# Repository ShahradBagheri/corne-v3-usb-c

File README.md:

# Corne Cherry v3 with a USB-C split link

Open `corne-cherry.kicad_pro` in KiCad 9. The project contains both original PCB halves in the original panel. J1 and J3 are now GCT USB4105-GF-A receptacles at the inside edges.

## Connecting the keyboard

With the keyboard unpowered, connect the two ports marked **SPLIT ONLY** using a USB-C to USB-C cable that carries USB 2.0 data. Then connect one controller's own USB port to the computer. Disconnect the computer cable before plugging or unplugging the split cable. Keep both split ports away from computers, chargers, and other USB devices. Power the keyboard from one controller at a time.

The receptacles carry the original Corne single-wire serial protocol over the cable. They have no USB enumeration, Type-C role detection, power negotiation, or isolation. No firmware change is required for the stock wired Corne v3 serial configuration.

| Receptacle contacts | Function |
| --- | --- |
| A4, A9, B4, B9 | Shared controller supply (VCC and VDD on the two halves) |
| A1, A12, B1, B12 and shell | Ground |
| A6 and B6 | Original serial data (USB 2.0 D+ conductor) |
| D−, CC1, CC2, SBU1 and SBU2 | Open |

## Mechanical and electrical checks

All 753 original Edge.Cuts entities match the upstream board, including the perimeter, panel, and LED cutouts. The 170 other footprint placements and the mounting-hole geometry match the original. The USB-C plug shell and insertion opening have a different shape from the audio jack, so check the clearance of your specific case and plug.

KiCad 9 reports zero schematic ERC violations, zero PCB unconnected items, and zero schematic-to-PCB parity issues. The PCB still reports legacy outline, copper-to-edge, and other DRC findings on the original layout, and library mismatch warnings for customized footprints. The USB4105 hole-to-copper exception is scoped to the manufacturer's locating-hole and contact geometry within each connector. The board has not been fabricated or tested. Review the outline and DRC with your board house before ordering.

## Sources

- [Original Corne Cherry v3.0.0 release by foostan](https://github.com/foostan/crkbd/releases/tag/corne-cherry-v3.0.0), commit `ad3892b7500d9b15100ee98f2aa5c35297481b0f`.
- [Corne Cherry v3 build guide](https://github.com/foostan/crkbd/blob/main/docs/corne-cherry/v3/buildguide_en.md).
- [GCT USB4105 series drawing](https://gct.co/files/drawings/usb4105.pdf).

The original project and its bundled footprint library retain their respective license notices.

### Original case fit review

The original v3 PCB perimeter, mounting centers, switch positions and 1.6 mm PCB thickness carry over. Both new port centerlines are at panel Y = 76.05 mm. Relative to the old TRRS axes, move each case opening approximately 1.8 mm toward the thumb keys. The shell is 8.94 mm wide and projects approximately 0.99 mm past the PCB edge. Allow for the plug overmold if the wall is recessed.

The closest lower mounting-hole centers are 2.25 mm (left) and 2.27 mm (right) from the USB-C shell outline in plan. A 4 mm diameter cylindrical post at those centers therefore clears the shell by approximately 0.25 mm nominal. Wider bosses, case ribs, tolerances and cable overmolds require the specific enclosure drawing or a physical fit test.

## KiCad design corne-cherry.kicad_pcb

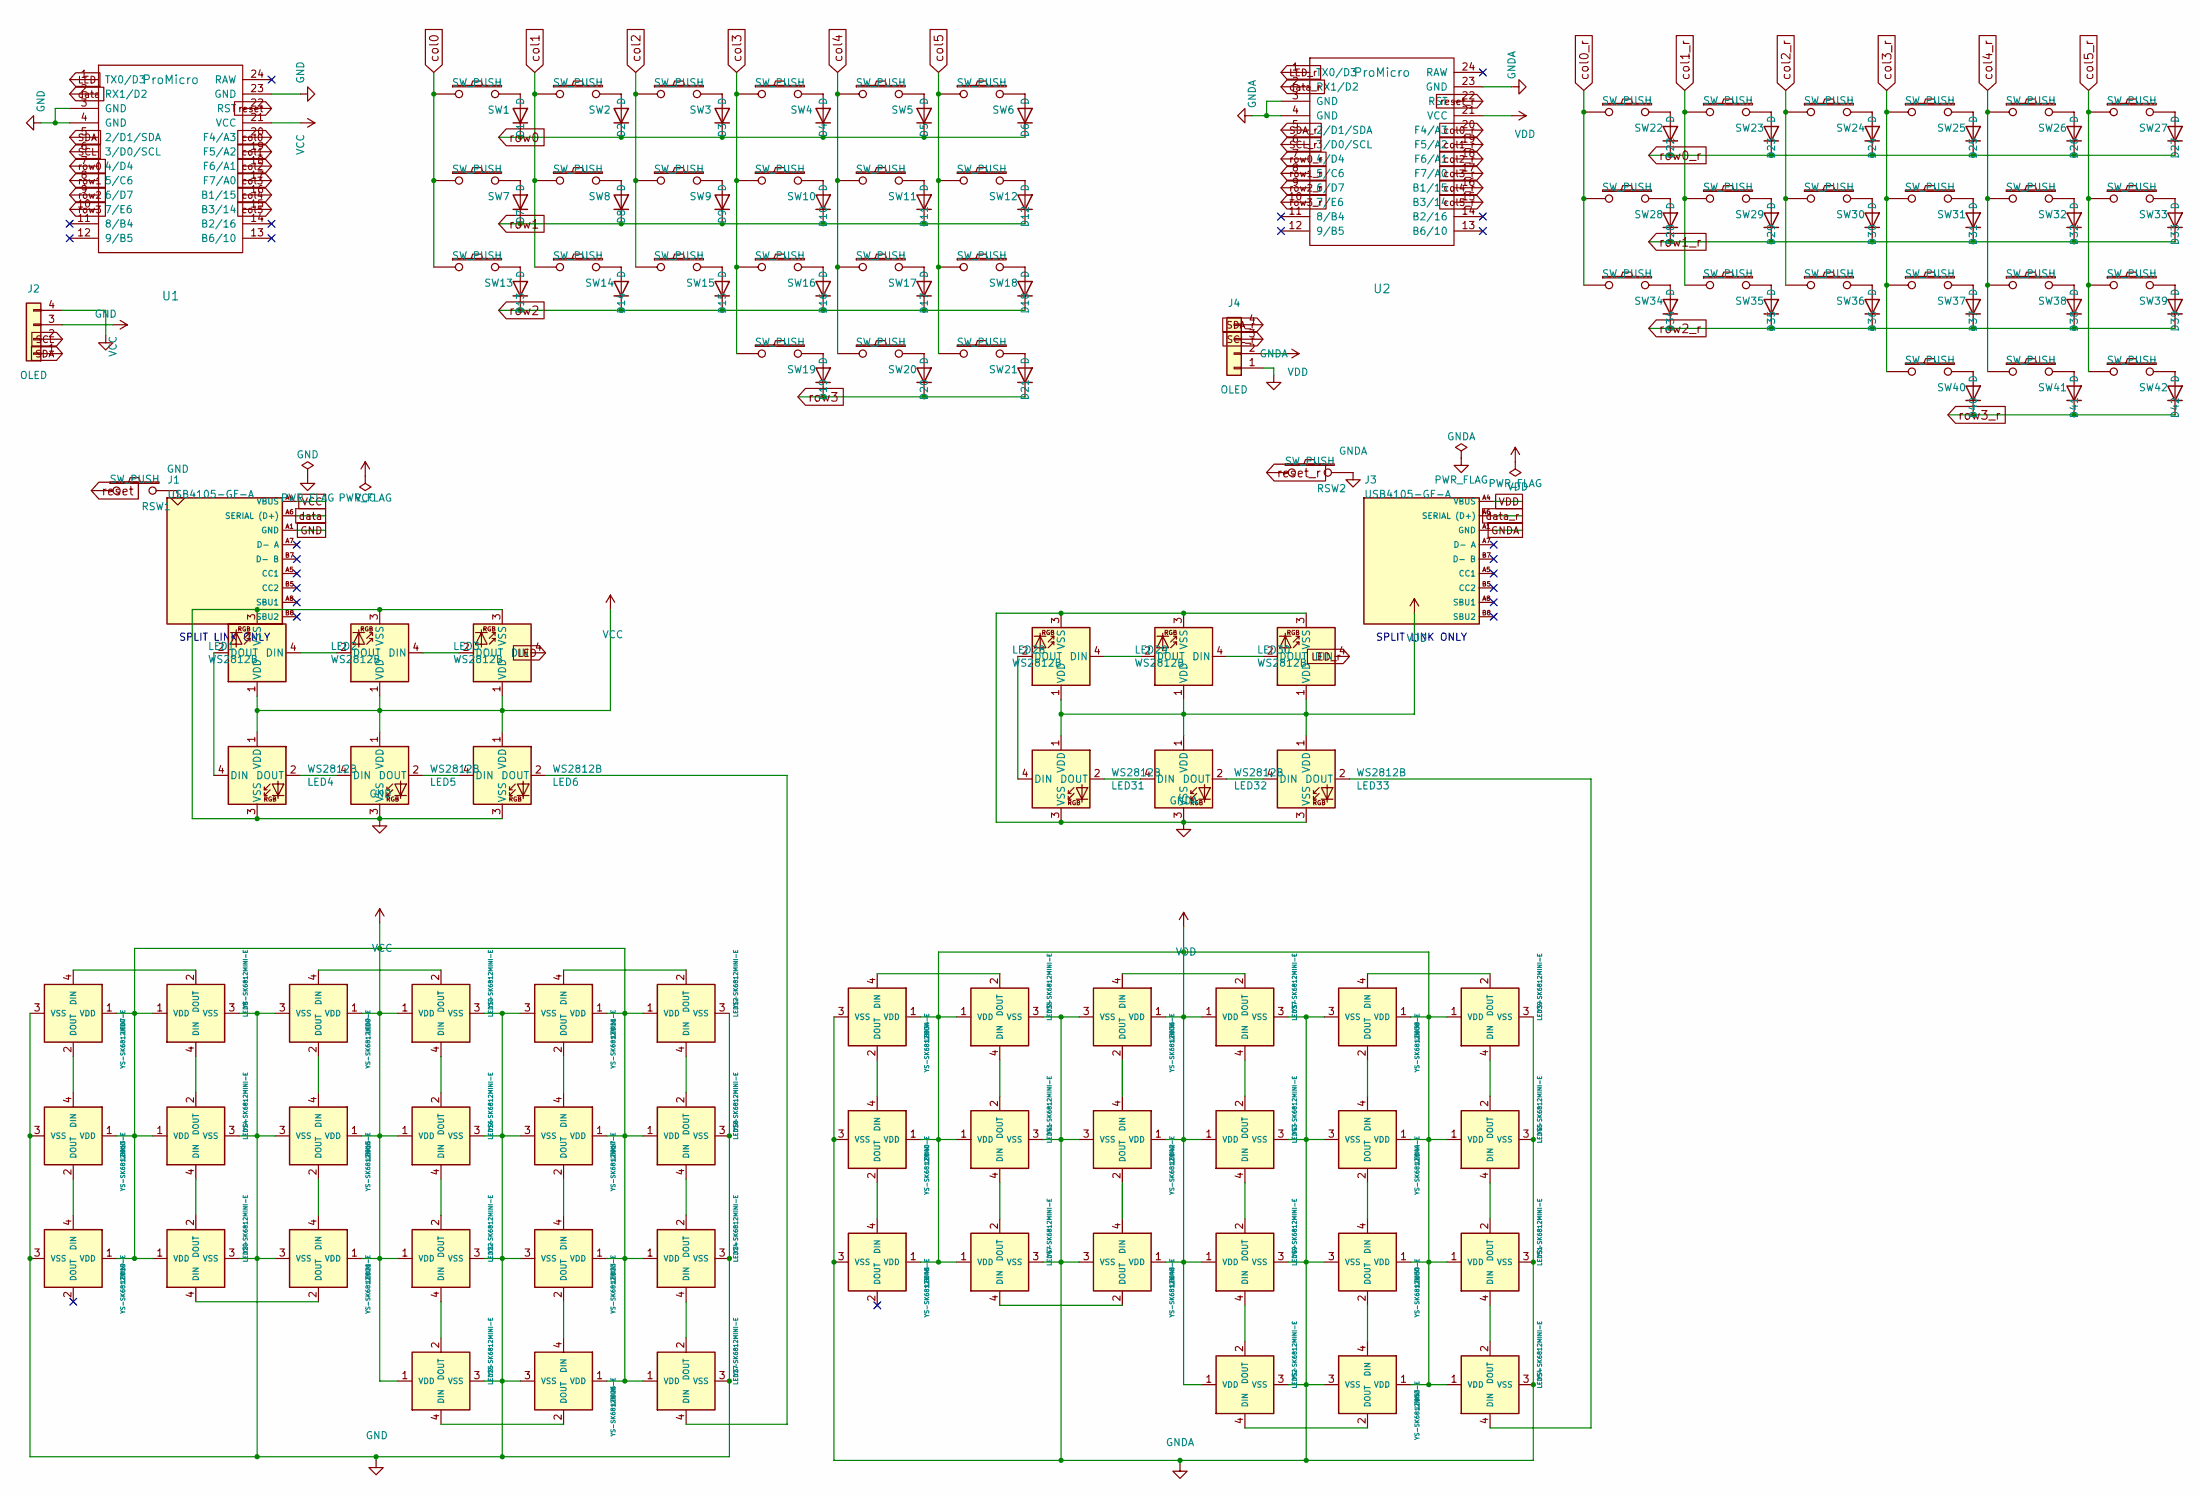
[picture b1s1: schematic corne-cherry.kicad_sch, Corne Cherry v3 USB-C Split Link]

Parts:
D1, D2, D3, D4, D5, D6, D7, D8, D9, D10, D11, D12, D13, D14, D15, D16, D17, D18, D19, D20, D21, D22, D23, D24, D25, D26, D27, D28, D29, D30, D31, D32, D33, D34, D35, D36, D37, D38, D39, D40, D41, D42: D; D3_SMD_v2
J1, J3: USB4105-GF-A; USB_C_Receptacle_GCT_USB4105-xx-A_16P_TopMnt_Horizontal
J2, J4: OLED; OLED_1side
LED1, LED2, LED3, LED4, LED5, LED6, LED28, LED29, LED30, LED31, LED32, LED33: WS2812B; LED_WS2812B_PLCC4_5.0x5.0mm_P3.2mm
LED7, LED8, LED9, LED10, LED11, LED12, LED13, LED14, LED15, LED16, LED17, LED18, LED19, LED20, LED21, LED22, LED23, LED24, LED25, LED26, LED27, LED34, LED35, LED36, LED37, LED38, LED39, LED40, LED41, LED42, LED43, LED44, LED45, LED46, LED47, LED48, LED49, LED50, LED51, LED52, LED53, LED54: YS-SK6812MINI-E
RSW1, RSW2: SW_PUSH; ResetSW_1side
SW1, SW2, SW3, SW4, SW5, SW6, SW7, SW8, SW9, SW10, SW11, SW12, SW13, SW14, SW15, SW16, SW17, SW18, SW19, SW20, SW22, SW23, SW24, SW25, SW26, SW27, SW28, SW29, SW30, SW31, SW32, SW33, SW34, SW35, SW36, SW37, SW38, SW39, SW40, SW41: SW_PUSH; CherryMX_Hotswap
SW21, SW42: SW_PUSH; CherryMX_Hotswap_1.5u
U1, U2: ProMicro; ProMicro_v3

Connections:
GND: J1.A1 (GND), J1.A12 (GND), J1.B1 (GND), J1.B12 (GND), J1.S1 (GND), J2.4, LED1.3 (VSS), LED2.3 (VSS), LED3.3 (VSS), LED4.3 (VSS), LED5.3 (VSS), LED6.3 (VSS), LED7.3 (VSS), LED8.3 (VSS), LED9.3 (VSS), LED10.3 (VSS), LED11.3 (VSS), LED12.3 (VSS), LED13.3 (VSS), LED14.3 (VSS), LED15.3 (VSS), LED16.3 (VSS), LED17.3 (VSS), LED18.3 (VSS), LED19.3 (VSS), LED20.3 (VSS), LED21.3 (VSS), LED22.3 (VSS), LED23.3 (VSS), LED24.3 (VSS), LED25.3 (VSS), LED26.3 (VSS), LED27.3 (VSS), RSW1.2, U1.3 (GND), U1.4 (GND), U1.23 (GND)
GNDA: J3.A1 (GND), J3.A12 (GND), J3.B1 (GND), J3.B12 (GND), J3.S1 (GND), J4.1, LED28.3 (VSS), LED29.3 (VSS), LED30.3 (VSS), LED31.3 (VSS), LED32.3 (VSS), LED33.3 (VSS), LED34.3 (VSS), LED35.3 (VSS), LED36.3 (VSS), LED37.3 (VSS), LED38.3 (VSS), LED39.3 (VSS), LED40.3 (VSS), LED41.3 (VSS), LED42.3 (VSS), LED43.3 (VSS), LED44.3 (VSS), LED45.3 (VSS), LED46.3 (VSS), LED47.3 (VSS), LED48.3 (VSS), LED49.3 (VSS), LED50.3 (VSS), LED51.3 (VSS), LED52.3 (VSS), LED53.3 (VSS), LED54.3 (VSS), RSW2.2, U2.3 (GND), U2.4 (GND), U2.23 (GND)
LED: LED3.4 (DIN), U1.1 (TX0/D3)
LED_r: LED30.4 (DIN), U2.1 (TX0/D3)
unnamed: D1.2 (A), SW1.2
unnamed: D2.2 (A), SW2.2
unnamed: D3.2 (A), SW3.2
unnamed: D4.2 (A), SW4.2
unnamed: D5.2 (A), SW5.2
unnamed: D6.2 (A), SW6.2
unnamed: D7.2 (A), SW7.2
unnamed: D8.2 (A), SW8.2
unnamed: D9.2 (A), SW9.2
unnamed: D10.2 (A), SW10.2
unnamed: D11.2 (A), SW11.2
unnamed: D12.2 (A), SW12.2
unnamed: D13.2 (A), SW13.2
unnamed: D14.2 (A), SW14.2
unnamed: D15.2 (A), SW15.2
unnamed: D16.2 (A), SW16.2
unnamed: D17.2 (A), SW17.2
unnamed: D18.2 (A), SW18.2
unnamed: D19.2 (A), SW19.2
unnamed: D20.2 (A), SW20.2
unnamed: D21.2 (A), SW21.2
unnamed: D22.2 (A), SW22.2
unnamed: D23.2 (A), SW23.2
unnamed: D24.2 (A), SW24.2
unnamed: D25.2 (A), SW25.2
unnamed: D26.2 (A), SW26.2
unnamed: D27.2 (A), SW27.2
unnamed: D28.2 (A), SW28.2
unnamed: D29.2 (A), SW29.2
unnamed: D30.2 (A), SW30.2
unnamed: D31.2 (A), SW31.2
unnamed: D32.2 (A), SW32.2
unnamed: D33.2 (A), SW33.2
unnamed: D34.2 (A), SW34.2
unnamed: D35.2 (A), SW35.2
unnamed: D36.2 (A), SW36.2
unnamed: D37.2 (A), SW37.2
unnamed: D38.2 (A), SW38.2
unnamed: D39.2 (A), SW39.2
unnamed: D40.2 (A), SW40.2
unnamed: D41.2 (A), SW41.2
unnamed: D42.2 (A), SW42.2
unnamed: LED1.4 (DIN), LED2.2 (DOUT)
unnamed: LED1.2 (DOUT), LED4.4 (DIN)
unnamed: LED2.4 (DIN), LED3.2 (DOUT)
unnamed: LED4.2 (DOUT), LED5.4 (DIN)
unnamed: LED5.2 (DOUT), LED6.4 (DIN)
unnamed: LED7.4 (DIN), LED8.2 (DOUT)
unnamed: LED10.4 (DIN), LED16.2 (DOUT)
unnamed: LED9.4 (DIN), LED10.2 (DOUT)
unnamed: LED11.4 (DIN), LED12.2 (DOUT)
unnamed: LED11.2 (DOUT), LED17.4 (DIN)
unnamed: LED12.4 (DIN), LED18.2 (DOUT)
unnamed: LED7.2 (DOUT), LED13.4 (DIN)
unnamed: LED13.2 (DOUT), LED19.4 (DIN)
unnamed: LED14.4 (DIN), LED20.2 (DOUT)
unnamed: LED8.4 (DIN), LED14.2 (DOUT)
unnamed: LED9.2 (DOUT), LED15.4 (DIN)
unnamed: LED15.2 (DOUT), LED21.4 (DIN)
unnamed: LED16.4 (DIN), LED22.2 (DOUT)
unnamed: LED17.2 (DOUT), LED23.4 (DIN)
unnamed: LED18.4 (DIN), LED24.2 (DOUT)
unnamed: LED20.4 (DIN), LED21.2 (DOUT)
unnamed: LED22.4 (DIN), LED25.2 (DOUT)
unnamed: LED23.2 (DOUT), LED26.4 (DIN)
unnamed: LED24.4 (DIN), LED27.2 (DOUT)
unnamed: LED25.4 (DIN), LED26.2 (DOUT)
unnamed: LED6.2 (DOUT), LED27.4 (DIN)
unnamed: LED28.4 (DIN), LED29.2 (DOUT)
unnamed: LED28.2 (DOUT), LED31.4 (DIN)
unnamed: LED29.4 (DIN), LED30.2 (DOUT)
unnamed: LED31.2 (DOUT), LED32.4 (DIN)
unnamed: LED32.2 (DOUT), LED33.4 (DIN)
unnamed: LED33.2 (DOUT), LED54.4 (DIN)
unnamed: LED34.4 (DIN), LED35.2 (DOUT)
unnamed: LED34.2 (DOUT), LED40.4 (DIN)
unnamed: LED35.4 (DIN), LED41.2 (DOUT)
unnamed: LED36.4 (DIN), LED37.2 (DOUT)
unnamed: LED36.2 (DOUT), LED42.4 (DIN)
unnamed: LED37.4 (DIN), LED43.2 (DOUT)
unnamed: LED38.4 (DIN), LED39.2 (DOUT)
unnamed: LED38.2 (DOUT), LED44.4 (DIN)
unnamed: LED39.4 (DIN), LED45.2 (DOUT)
unnamed: LED40.2 (DOUT), LED46.4 (DIN)
unnamed: LED41.4 (DIN), LED47.2 (DOUT)
unnamed: LED42.2 (DOUT), LED48.4 (DIN)
unnamed: LED43.4 (DIN), LED49.2 (DOUT)
unnamed: LED44.2 (DOUT), LED50.4 (DIN)
unnamed: LED45.4 (DIN), LED51.2 (DOUT)
unnamed: LED47.4 (DIN), LED48.2 (DOUT)
unnamed: LED49.4 (DIN), LED52.2 (DOUT)
unnamed: LED50.2 (DOUT), LED53.4 (DIN)
unnamed: LED51.4 (DIN), LED54.2 (DOUT)
unnamed: LED52.4 (DIN), LED53.2 (DOUT)
SCL: J2.2, U1.6 (3/D0/SCL)
SCL_r: J4.3, U2.6 (3/D0/SCL)
SDA: J2.1, U1.5 (2/D1/SDA)
SDA_r: J4.4, U2.5 (2/D1/SDA)
VCC: J1.A4 (VBUS), J1.A9 (VBUS), J1.B4 (VBUS), J1.B9 (VBUS), J2.3, LED1.1 (VDD), LED2.1 (VDD), LED3.1 (VDD), LED4.1 (VDD), LED5.1 (VDD), LED6.1 (VDD), LED7.1 (VDD), LED8.1 (VDD), LED9.1 (VDD), LED10.1 (VDD), LED11.1 (VDD), LED12.1 (VDD), LED13.1 (VDD), LED14.1 (VDD), LED15.1 (VDD), LED16.1 (VDD), LED17.1 (VDD), LED18.1 (VDD), LED19.1 (VDD), LED20.1 (VDD), LED21.1 (VDD), LED22.1 (VDD), LED23.1 (VDD), LED24.1 (VDD), LED25.1 (VDD), LED26.1 (VDD), LED27.1 (VDD), U1.21 (VCC)
VDD: J3.A4 (VBUS), J3.A9 (VBUS), J3.B4 (VBUS), J3.B9 (VBUS), J4.2, LED28.1 (VDD), LED29.1 (VDD), LED30.1 (VDD), LED31.1 (VDD), LED32.1 (VDD), LED33.1 (VDD), LED34.1 (VDD), LED35.1 (VDD), LED36.1 (VDD), LED37.1 (VDD), LED38.1 (VDD), LED39.1 (VDD), LED40.1 (VDD), LED41.1 (VDD), LED42.1 (VDD), LED43.1 (VDD), LED44.1 (VDD), LED45.1 (VDD), LED46.1 (VDD), LED47.1 (VDD), LED48.1 (VDD), LED49.1 (VDD), LED50.1 (VDD), LED51.1 (VDD), LED52.1 (VDD), LED53.1 (VDD), LED54.1 (VDD), U2.21 (VCC)
col0: SW1.1, SW7.1, SW13.1, U1.20 (F4/A3)
col0_r: SW22.1, SW28.1, SW34.1, U2.20 (F4/A3)
col1: SW2.1, SW8.1, SW14.1, U1.19 (F5/A2)
col1_r: SW23.1, SW29.1, SW35.1, U2.19 (F5/A2)
col2: SW3.1, SW9.1, SW15.1, U1.18 (F6/A1)
col2_r: SW24.1, SW30.1, SW36.1, U2.18 (F6/A1)
col3: SW4.1, SW10.1, SW16.1, SW19.1, U1.17 (F7/A0)
col3_r: SW25.1, SW31.1, SW37.1, SW40.1, U2.17 (F7/A0)
col4: SW5.1, SW11.1, SW17.1, SW20.1, U1.16 (B1/15)
col4_r: SW26.1, SW32.1, SW38.1, SW41.1, U2.16 (B1/15)
col5: SW6.1, SW12.1, SW18.1, SW21.1, U1.15 (B3/14)
col5_r: SW27.1, SW33.1, SW39.1, SW42.1, U2.15 (B3/14)
data: J1.A6 (SERIAL_(D+)), J1.B6 (SERIAL_(D+)), U1.2 (RX1/D2)
data_r: J3.A6 (SERIAL_(D+)), J3.B6 (SERIAL_(D+)), U2.2 (RX1/D2)
reset: RSW1.1, U1.22 (RST)
reset_r: RSW2.1, U2.22 (RST)
row0: D1.1 (K), D2.1 (K), D3.1 (K), D4.1 (K), D5.1 (K), D6.1 (K), U1.7 (4/D4)
row0_r: D22.1 (K), D23.1 (K), D24.1 (K), D25.1 (K), D26.1 (K), D27.1 (K), U2.7 (4/D4)
row1: D7.1 (K), D8.1 (K), D9.1 (K), D10.1 (K), D11.1 (K), D12.1 (K), U1.8 (5/C6)
row1_r: D28.1 (K), D29.1 (K), D30.1 (K), D31.1 (K), D32.1 (K), D33.1 (K), U2.8 (5/C6)
row2: D13.1 (K), D14.1 (K), D15.1 (K), D16.1 (K), D17.1 (K), D18.1 (K), U1.9 (6/D7)
row2_r: D34.1 (K), D35.1 (K), D36.1 (K), D37.1 (K), D38.1 (K), D39.1 (K), U2.9 (6/D7)
row3: D19.1 (K), D20.1 (K), D21.1 (K), U1.10 (7/E6)
row3_r: D40.1 (K), D41.1 (K), D42.1 (K), U2.10 (7/E6)

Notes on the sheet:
SPLIT LINK ONLY

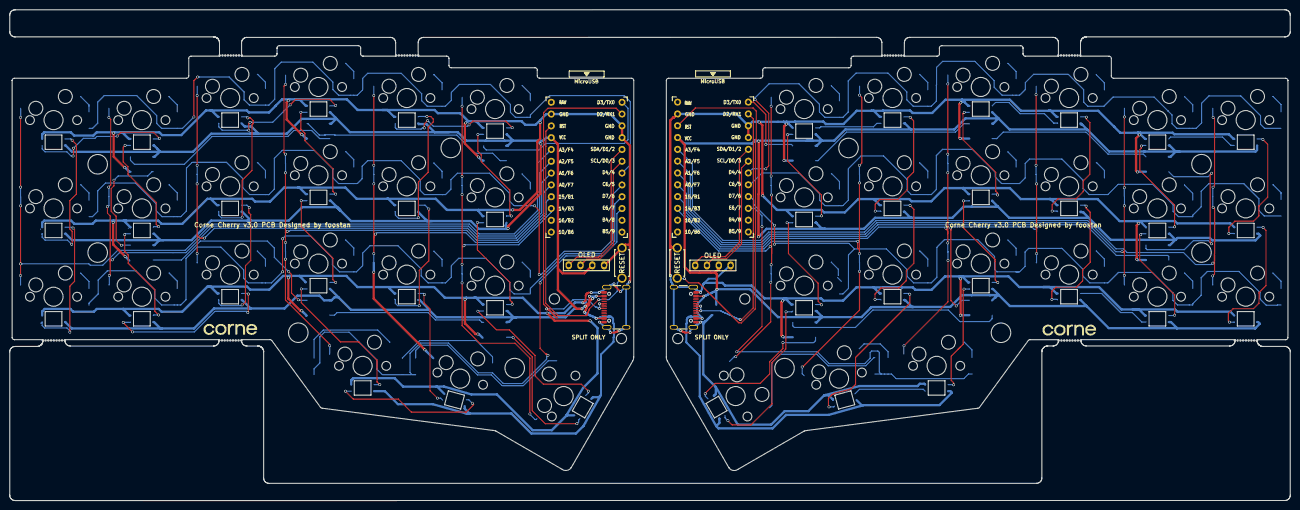
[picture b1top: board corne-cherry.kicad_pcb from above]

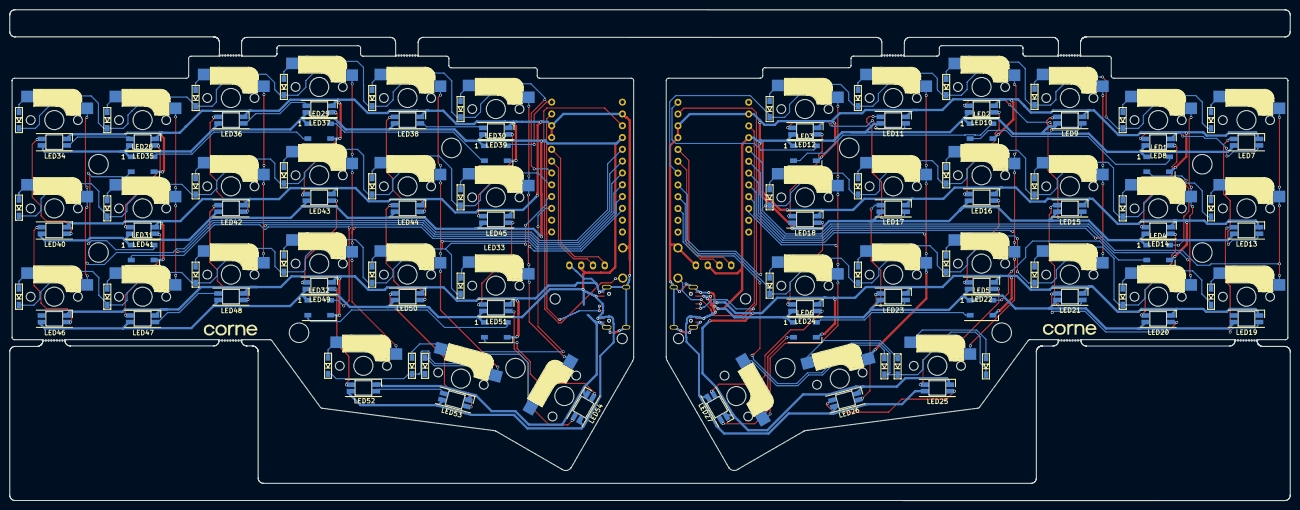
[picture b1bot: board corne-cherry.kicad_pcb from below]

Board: 2 copper layers, 275.5 x 105.6 mm, 160 parts (103 on the bottom side), 128 nets.

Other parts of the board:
Ref**: Val**; M2_HOLE_v2
Ref**#2, Ref**#3, Ref**#4, Ref**#5, Ref**#6, Ref**#7, Ref**#8, Ref**#9, Ref**#10, Ref**#11, Ref**#12, Ref**#13, Ref**#14: Val**; M2_HOLE_v2
